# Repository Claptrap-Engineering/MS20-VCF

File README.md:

# MS20-VCF
6HP eurorack SMD version of the famous MS20 Voltage controlled filter.

Based on the work of other community members as René Schmitz, Look Mum No Computer, Eddy Bergman, KORG and many others.

You can find the mouser bom here (you might want to add the desired potmeters).
https://www.mouser.com/ProjectManager/ProjectDetail.aspx?AccessID=ca94445cf4

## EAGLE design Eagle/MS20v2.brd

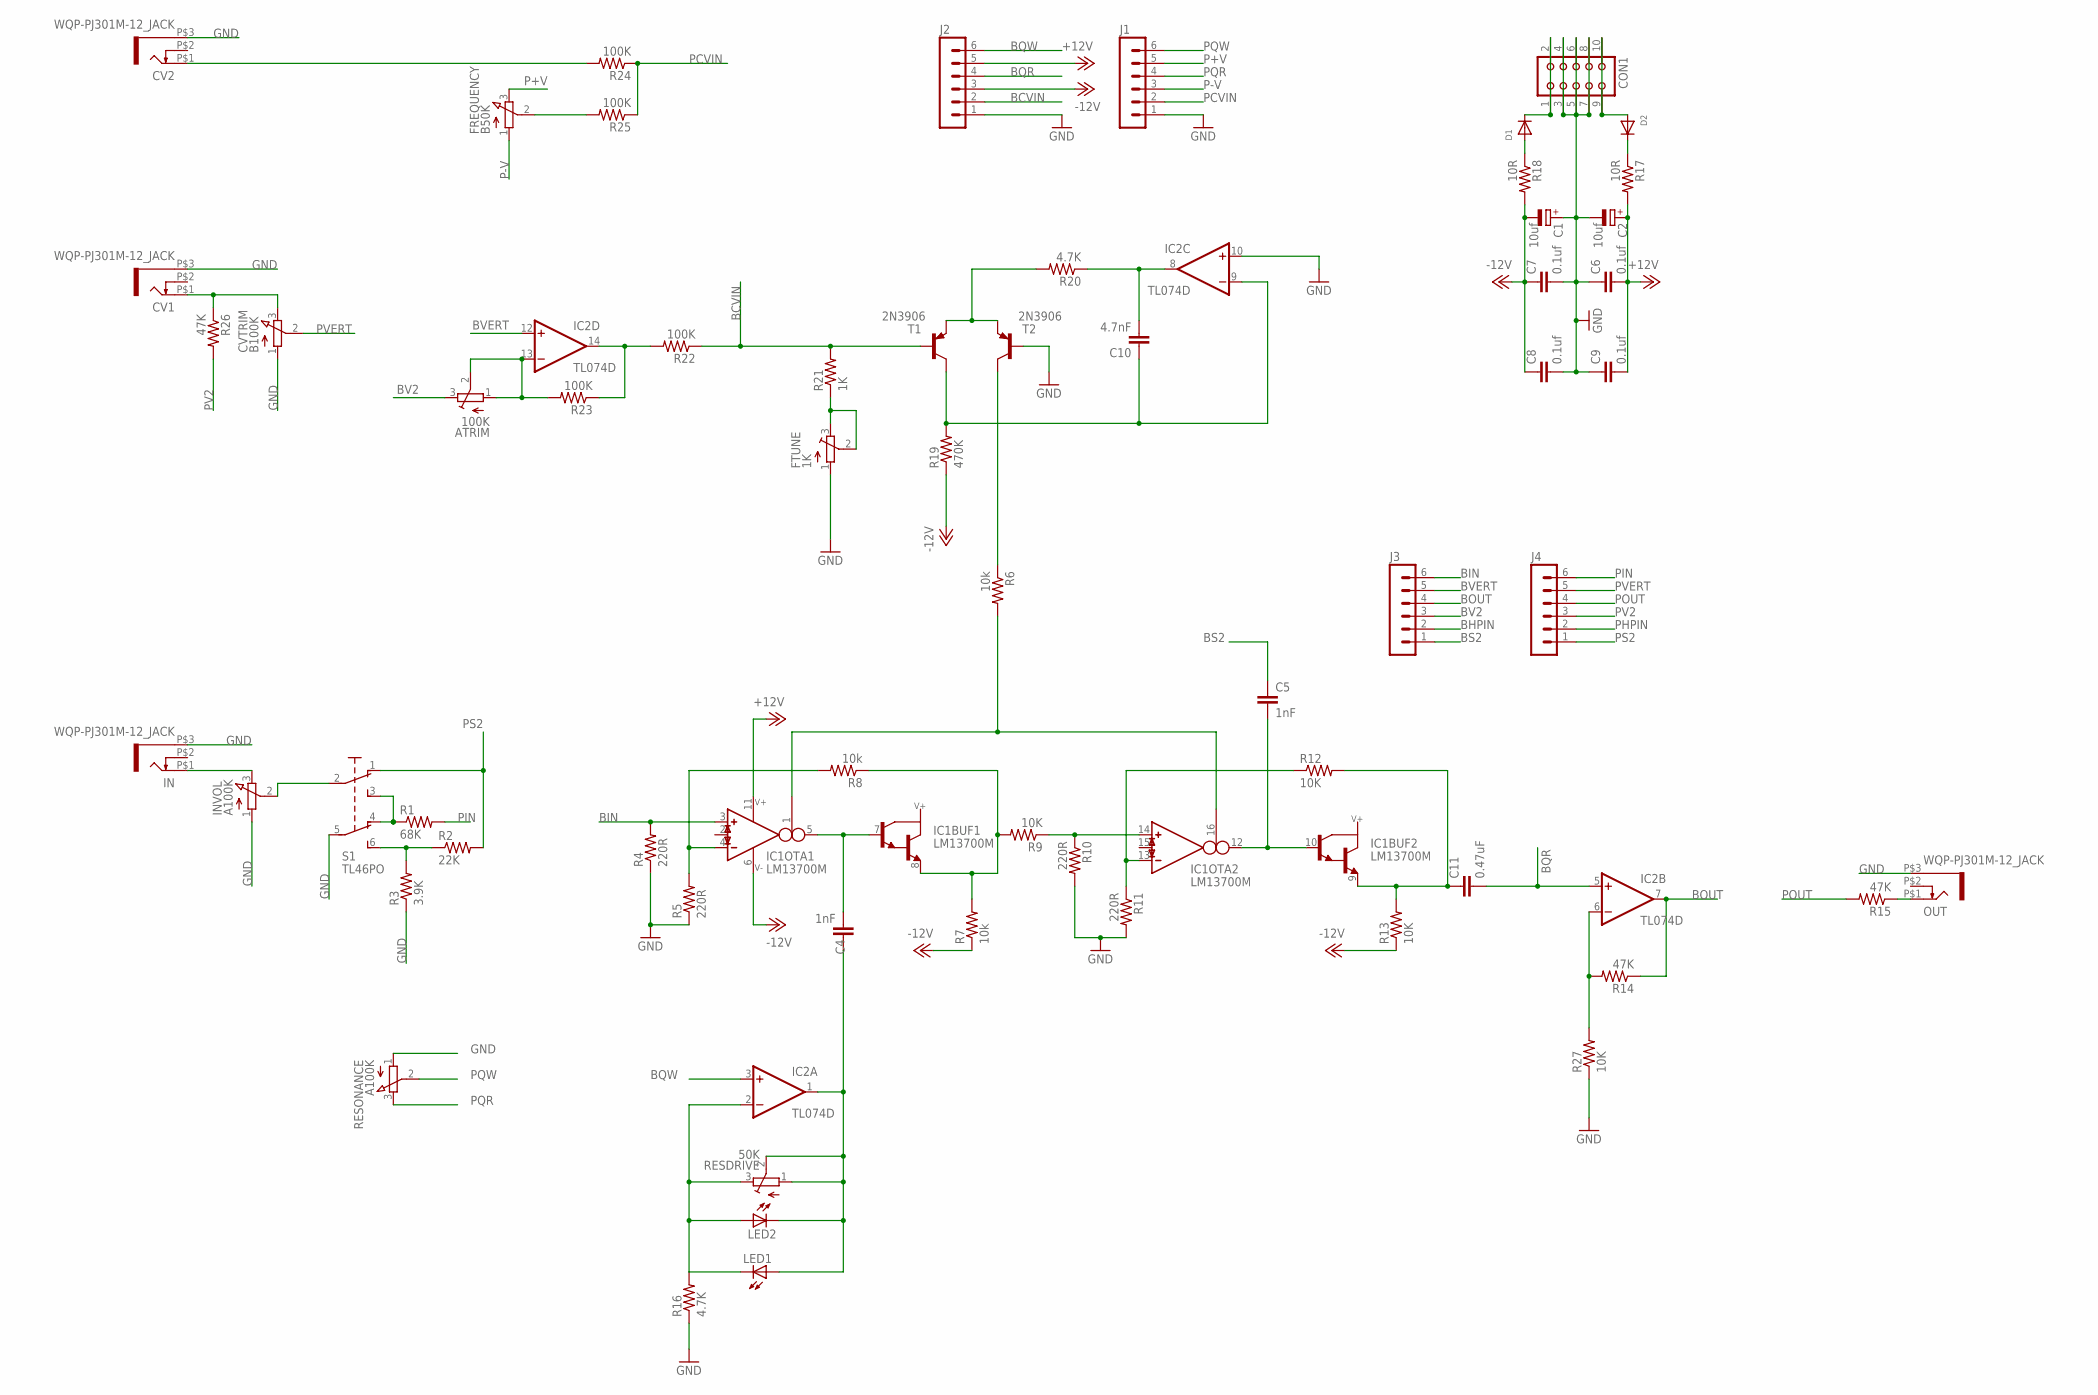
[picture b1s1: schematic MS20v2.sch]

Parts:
ATRIM: 100K; TC33X
C1, C2: 10uf; 153CLV-0405
C4, C5: 1nF; C0603
C6, C7, C8, C9: 0.1uf; C0603
C10: 4.7nF; C0603
C11: 0.47uF; C0603
CON1: CON10
CV1, CV2: WQP-PJ301M-12_JACK
CVTRIM: B100K; EVUF
D1, D2: DIODESOD-123; SOD-123
FREQUENCY: B50K; EVUF
FTUNE: 1K; TC33X
IC1: LM13700M; SO16
IC2: TL074D; SO14
IN: WQP-PJ301M-12_JACK
INVOL: A100K; EVUF
J1, J2, J3, J4: MA06-1
LED1, LED2: LED3MM
OUT: WQP-PJ301M-12_JACK
R1: 68K; R0603
R2: 22K; R0603
R3: 3.9K; R0603
R4, R5, R10, R11: 220R; R0603
R6, R7, R8: 10k; R0603
R9, R12, R13, R27: 10K; R0603
R14, R15, R26: 47K; R0603
R16, R20: 4.7K; R0603
R17, R18: 10R; R0603
R19: 470K; R0603
R21: 1K; R0603
R22, R23, R24, R25: 100K; R0603
RESDRIVE: 50K; TC33X
RESONANCE: A100K; EVUF
S1: TL46PO; TL4XPO
T1, T2: 2N3906; SOT23-BEC

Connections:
+12V: C2.+, C6.2, C9.2, IC1.11 (V+), IC2.4 (V+), J2.5, R17.2
-12V: C1.-, C7.1, C8.1, IC1.6 (V-), IC2.11 (V-), J2.3, R7.1, R13.1, R18.2, R19.1
BCVIN: J2.2, R21.2, R22.1, T1.B
BHPIN: J3.2
BIN: IC1.3 (IN_P), J3.6, R4.2
BOUT: IC2.7 (OUT), J3.4, R14.1
BQR: C11.2, IC2.5 (+IN), J2.4
BQW: IC2.3 (+IN), J2.6
BS2: C5.1, J3.1
BV2: ATRIM.3 (E), J3.3
BVERT: IC2.12 (+IN), J3.5
GND: C1.+, C2.-, C6.1, C7.2, C8.2, C9.1, CON1.3, CON1.4, CON1.5, CON1.6, CON1.7, CON1.8, CV1.P$3 (1), CV2.P$3 (1), CVTRIM.1 (A), FTUNE.1 (A), IC2.10 (+IN), IN.P$3 (1), INVOL.1 (A), J1.1, J2.1, OUT.P$3 (1), R3.1, R4.1, R5.1, R10.2, R11.2, R16.1, R27.1, RESONANCE.1 (A), S1.5 (P1), T2.B
unnamed: CON1.9, CON1.10, D2.A
unnamed: CON1.1, CON1.2, D1.C
unnamed: R1.1, S1.3 (S), S1.4 (O1)
unnamed: R2.1, R3.2, S1.6 (S1)
unnamed: D1.A, R18.1
unnamed: IC1.4 (IN_N), R5.2, R8.2
unnamed: CV1.P$1 (2), CVTRIM.3 (E), R26.1
unnamed: D2.C, R17.1
unnamed: IC1.13 (IN_N), R11.1, R12.1
unnamed: IC1.8 (E), R7.2, R8.1, R9.2
unnamed: C4.2, IC1.5 (OUT), IC1.7 (B)
unnamed: IC1.1 (I_BIAS), IC1.16 (I_BIAS), R6.2
unnamed: IC2.14 (OUT), R22.2, R23.1
unnamed: C4.1, IC2.1 (OUT), LED1.A, LED2.K (C), RESDRIVE.1 (A), RESDRIVE.2 (S)
unnamed: IC1.14 (IN_P), R9.1, R10.1
unnamed: C11.1, IC1.9 (E), R12.2, R13.2
unnamed: C5.2, IC1.10 (B), IC1.12 (OUT)
unnamed: IC2.6 (-IN), R14.2, R27.2
unnamed: R6.1, T2.C
unnamed: R20.2, T1.E, T2.E
unnamed: C10.2, IC2.8 (OUT), R20.1
unnamed: C10.1, IC2.9 (-IN), R19.2, T1.C
unnamed: IC2.2 (-IN), LED1.K (C), LED2.A, R16.2, RESDRIVE.3 (E)
unnamed: FTUNE.2 (S), FTUNE.3 (E), R21.1
unnamed: ATRIM.1 (A), ATRIM.2 (S), IC2.13 (-IN), R23.2
unnamed: CV2.P$1 (2), R24.2
unnamed: INVOL.2 (S), S1.2
unnamed: IN.P$1 (2), INVOL.3 (E)
unnamed: FREQUENCY.2 (S), R25.2
unnamed: OUT.P$1 (2), R15.1
P+V: FREQUENCY.3 (E), J1.5
P-V: FREQUENCY.1 (A), J1.3
PCVIN: J1.2, R24.1, R25.1
PHPIN: J4.2
PIN: J4.6, R1.2
POUT: J4.4, R15.2
PQR: J1.4, RESONANCE.3 (E)
PQW: J1.6, RESONANCE.2 (S)
PS2: J4.1, R2.2, S1.1 (O)
PV2: J4.3, R26.2
PVERT: CVTRIM.2 (S), J4.5

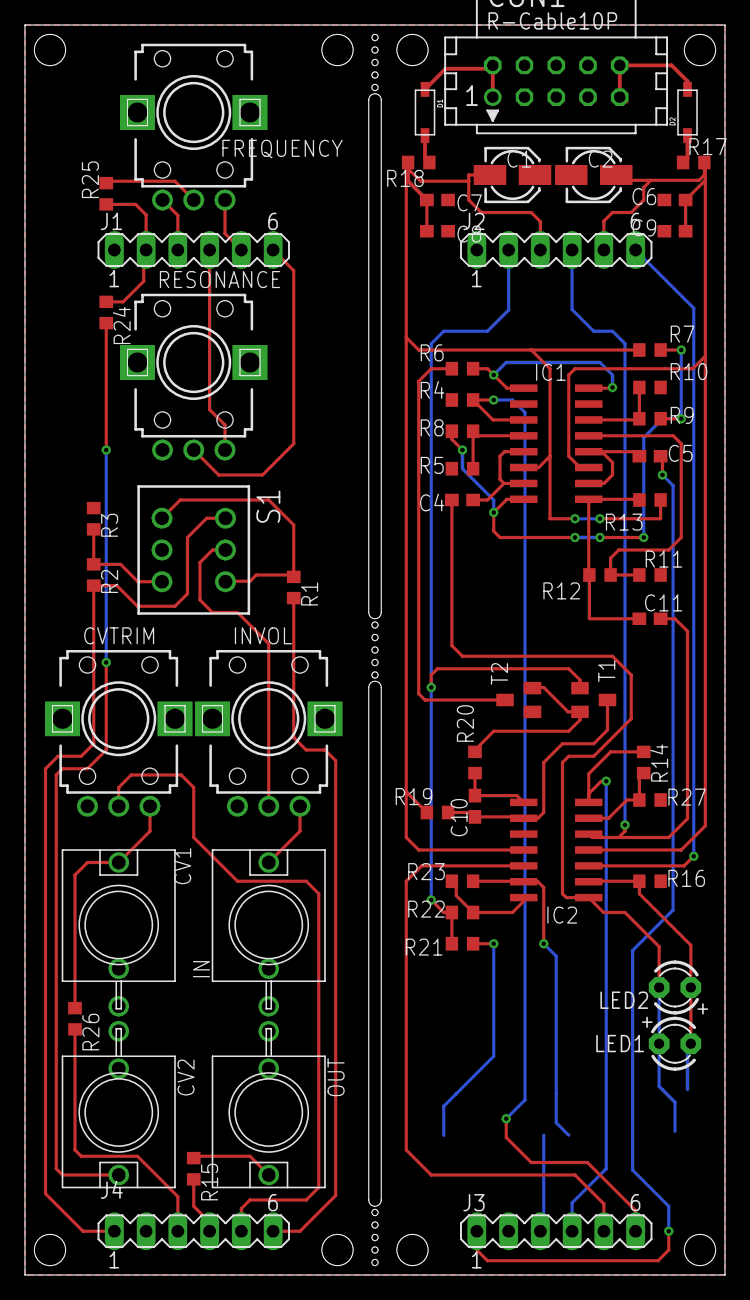
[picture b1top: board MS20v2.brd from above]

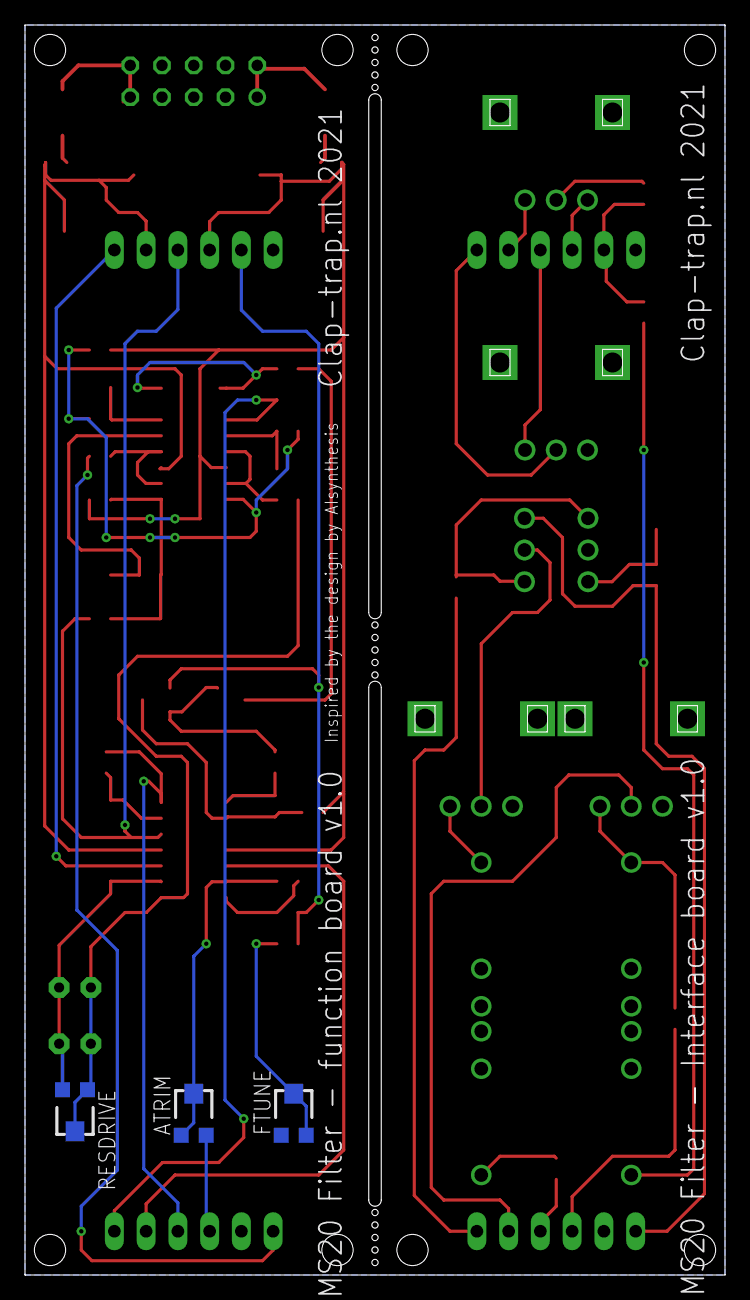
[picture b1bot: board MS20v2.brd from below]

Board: 2 copper layers, 56.0 x 100.0 mm, 62 parts (3 on the bottom side), 51 nets.

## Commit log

2021-04-30 first push
2021-05-26 updated drawing for readability
2021-05-26 updated Pot designations/values
2021-05-26 changed HP/LP switch type to TL46 P0
2021-05-31 front plate files
2021-05-31 exported frontplate files
2021-05-31 Changed 10uf cap to 0,47uf cap
